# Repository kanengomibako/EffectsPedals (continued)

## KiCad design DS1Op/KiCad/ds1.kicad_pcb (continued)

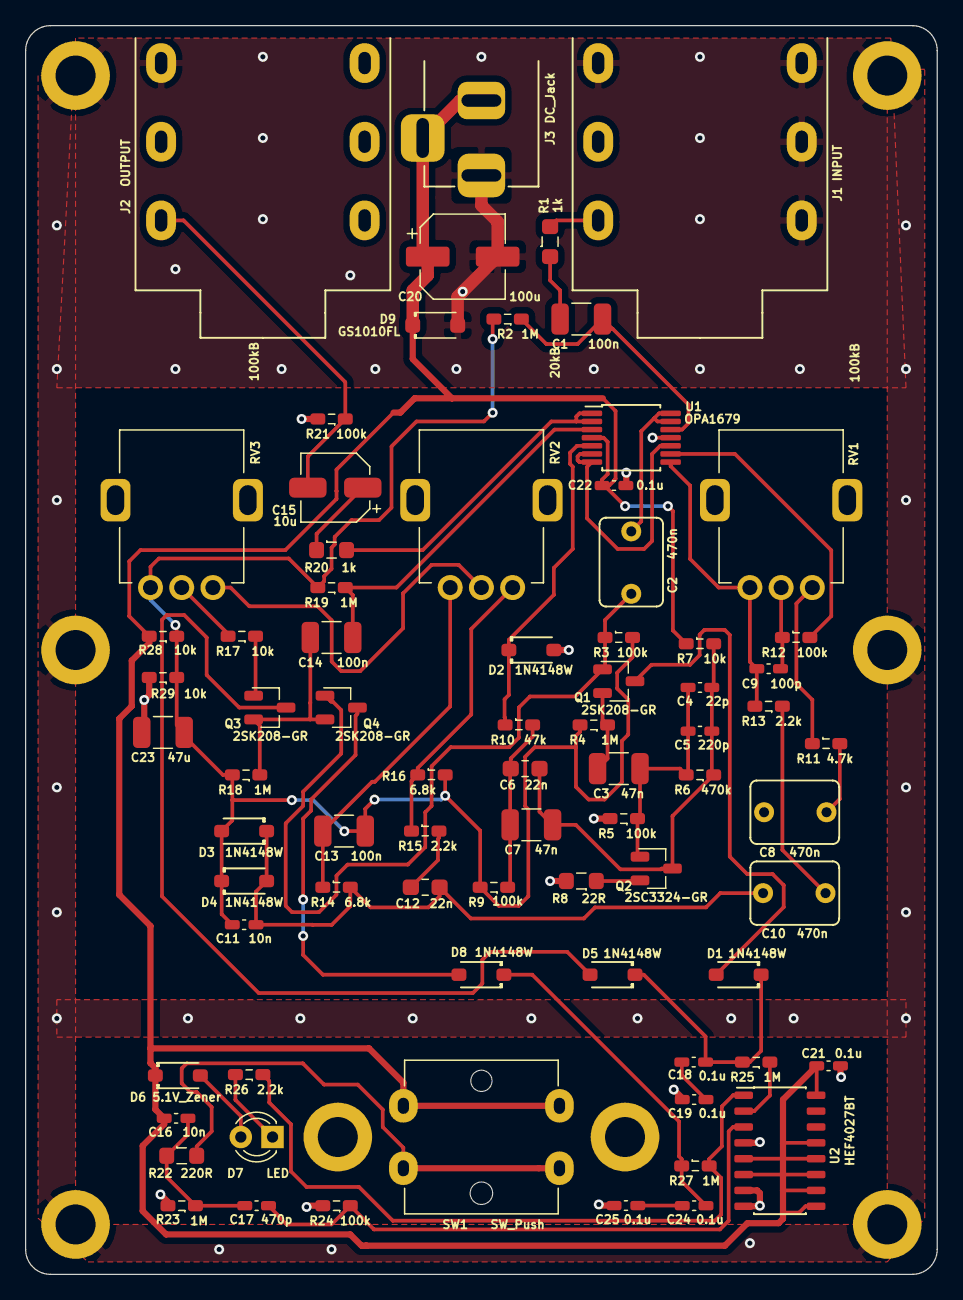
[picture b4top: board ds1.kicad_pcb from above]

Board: 2 copper layers, 73.0 x 100.0 mm, 76 parts (0 on the bottom side), 47 nets.
